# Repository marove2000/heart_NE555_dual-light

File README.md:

# Heart SMD NE555
24 LEDs forming a LED-Heart driven by a NE555 bistable vibrator. A LED-Light runs around the heart. The speed of the running LED-light can be modified by the potentiomenter
This soldering Kit requires first experience in SMD-Soldering and is a very good practice for the size 0805.

- Status: **Complete**
- Difficulty: **3/5**

### Parts List

| Description                   |  Name  | Quantity |
|-------------------------------|:------:|:--------:|
| SMD LED 0805 red              | D5-D28 |    24    |
| SMD Capacitor 10nF            |   C1   |     1    |
| SMD Capacitor 100n            |  C2,C3 |     2    |
| SMD Capacitor 1uF		|   C4	 |     1    |
| SMD Diode 1N4007              |  D1-D2 |     2    |
| SMD Push Button               |   SW1  |     1    |
| SMD Sliding Switch            |   SW2  |     1    |
| RV1 Potentiometer             |   RV1  |     1    |
| SMD Resistor 0805 1k          |   R2   |     1    |
| SMD Resistor 0805 100k        |   R3   |     1    |
| SMD Resistor 0805 47R         |   R5   |     1    |
| NE555 SOIC-8                  |   U1   |     1    |
| CD4017 SOP-16                 |  U2,U3 |     2    |
| CR2032 Battery Holder (SMD)   |   BT1  |     1    |
| CR2032 Battery (not included) |        |     1    |

### Manual
You can find the manual and pictures of every step here: https://github.com/Binary-Kitchen/SolderingTutorial

### Buy Kits

You can also buy a ready to make soldering-kit @ [shop.blinkyparts.com](https://shop.blinkyparts.com/de/SMD-LED-Herz-mit-NE555-SMD-Bausatz-mit-Herz/blink232542).

### Copyright and Authorship

- Board: [CC-BY-SA 4.0](https://creativecommons.org/licenses/by-sa/4.0/) - [Timo Schindler @ blinkyparts.com](https://shop.blinkyparts.com)
- CR2032 battery holder footprint: [CC-BY 4.0](https://creativecommons.org/licenses/by/4.0/) - Sparkfun (https://github.com/sparkfun/SparkFun-KiCad-Libraries)

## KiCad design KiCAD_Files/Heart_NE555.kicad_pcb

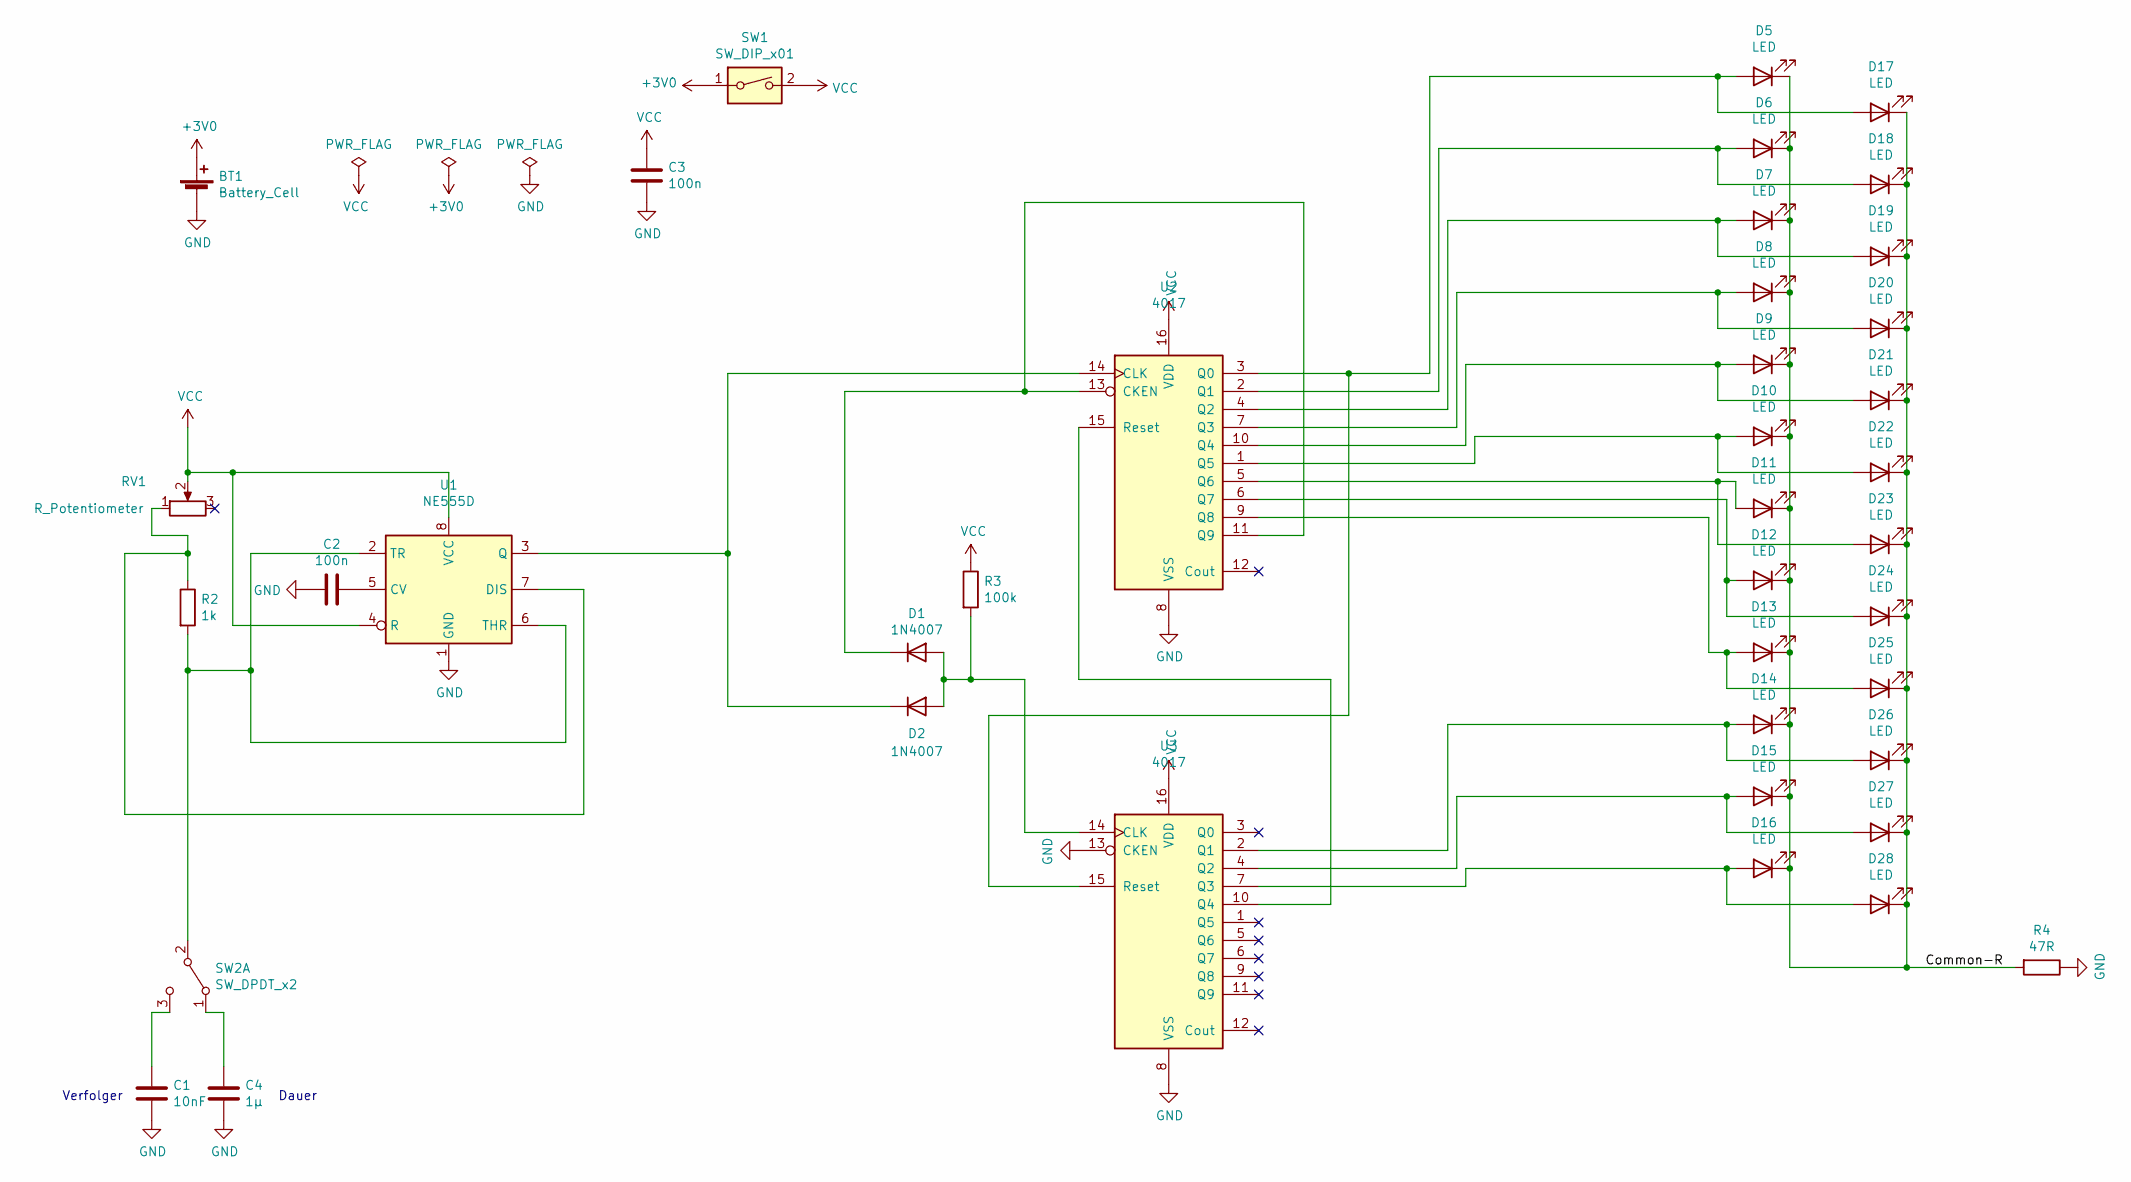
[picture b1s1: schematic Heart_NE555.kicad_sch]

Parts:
BT1: Battery_Cell; BatteryHolder_Keystone_1060_1x2032_HandSoldering
C1: 10nF; C_0805_2012Metric_Pad1.18x1.45mm_HandSolder
C2, C3: 100n; C_0805_2012Metric_Pad1.18x1.45mm_HandSolder
C4: 1µ; C_0805_2012Metric_Pad1.18x1.45mm_HandSolder
D1, D2: 1N4007; D_SOD-123_handsolder
D5, D6, D7, D8, D9, D10, D11, D12, D13, D14, D15, D16, D17, D18, D19, D20, D21, D22, D23, D24, D25, D26, D27, D28: LED; LED_0805_2012Metric_Pad1.15x1.40mm_HandSolder
R2: 1k; R_0805_2012Metric_Pad1.20x1.40mm_HandSolder
R3: 100k; R_0805_2012Metric_Pad1.20x1.40mm_HandSolder
R4: 47R; R_0805_2012Metric_Pad1.20x1.40mm_HandSolder
RV1: R_Potentiometer; Potentiometer_Vishay_TS53YJ_Vertical
SW1: SW_DIP_x01; Push_Button
SW2: SW_DPDT_x2; smd_switch_slide
U1: NE555D; SOIC-8_3.9x4.9mm_P1.27mm
U2, U3: 4017; SOP-16_4.4x10.4mm_P1.27mm

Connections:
+3V0: BT1.1 (+), SW1.1
/Common-R: D5.1 (K), D6.1 (K), D7.1 (K), D8.1 (K), D9.1 (K), D10.1 (K), D11.1 (K), D12.1 (K), D13.1 (K), D14.1 (K), D15.1 (K), D16.1 (K), D17.1 (K), D18.1 (K), D19.1 (K), D20.1 (K), D21.1 (K), D22.1 (K), D23.1 (K), D24.1 (K), D25.1 (K), D26.1 (K), D27.1 (K), D28.1 (K), R4.2
GND: BT1.2 (-), C1.2, C2.2, C3.2, C4.2, R4.1, U1.1 (GND), U2.8 (VSS), U3.8 (VSS), U3.13 (CKEN)
unnamed: C1.1, SW2.3 (C)
unnamed: C2.1, U1.5 (CV)
unnamed: C4.1, SW2.1 (A)
unnamed: D1.1 (K), U2.11 (Q9), U2.13 (CKEN)
unnamed: D1.2 (A), D2.2 (A), R3.2, U3.14 (CLK)
unnamed: D2.1 (K), U1.3 (Q), U2.14 (CLK)
unnamed: D10.2 (A), D22.2 (A), U2.1 (Q5)
unnamed: D11.2 (A), D23.2 (A), U2.5 (Q6)
unnamed: D12.2 (A), D24.2 (A), U2.6 (Q7)
unnamed: D13.2 (A), D25.2 (A), U2.9 (Q8)
unnamed: D14.2 (A), D26.2 (A), U3.2 (Q1)
unnamed: D15.2 (A), D27.2 (A), U3.4 (Q2)
unnamed: D16.2 (A), D28.2 (A), U3.7 (Q3)
unnamed: D5.2 (A), D17.2 (A), U2.3 (Q0), U3.15 (Reset)
unnamed: D6.2 (A), D18.2 (A), U2.2 (Q1)
unnamed: D7.2 (A), D19.2 (A), U2.4 (Q2)
unnamed: D8.2 (A), D20.2 (A), U2.7 (Q3)
unnamed: D9.2 (A), D21.2 (A), U2.10 (Q4)
unnamed: R2.1, RV1.1, U1.7 (DIS)
unnamed: R2.2, SW2.2 (B), U1.2 (TR), U1.6 (THR)
unnamed: U2.15 (Reset), U3.10 (Q4)
VCC: C3.1, R3.1, RV1.2, SW1.2, U1.4 (R), U1.8 (VCC), U2.16 (VDD), U3.16 (VDD)

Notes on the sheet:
Verfolger
Dauer

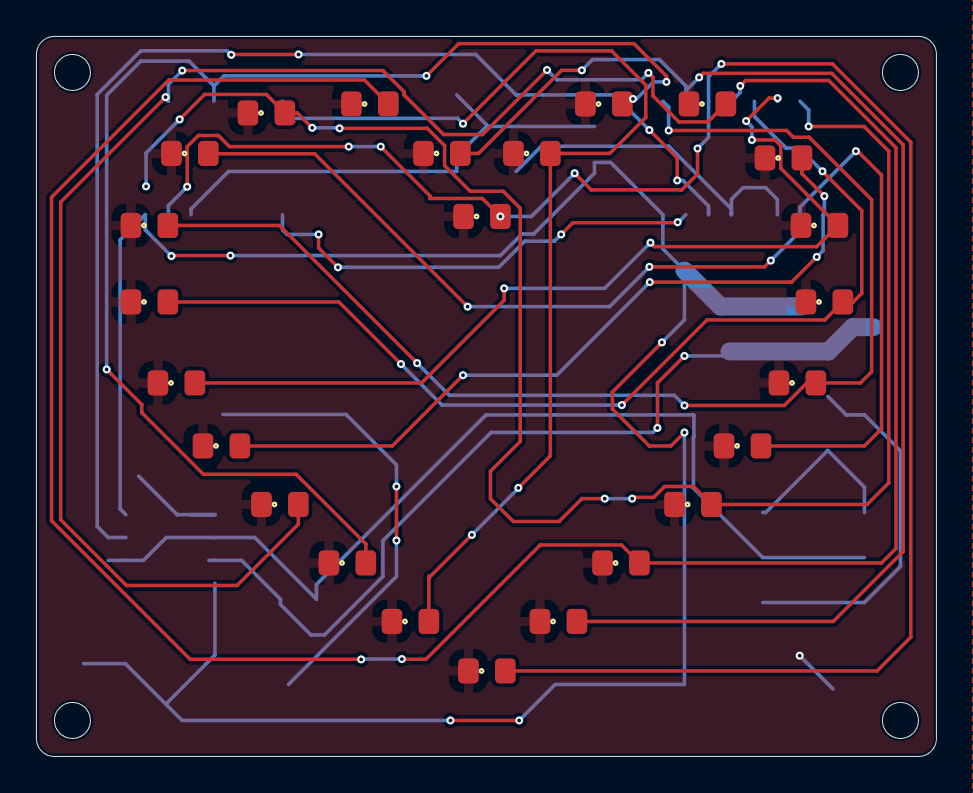
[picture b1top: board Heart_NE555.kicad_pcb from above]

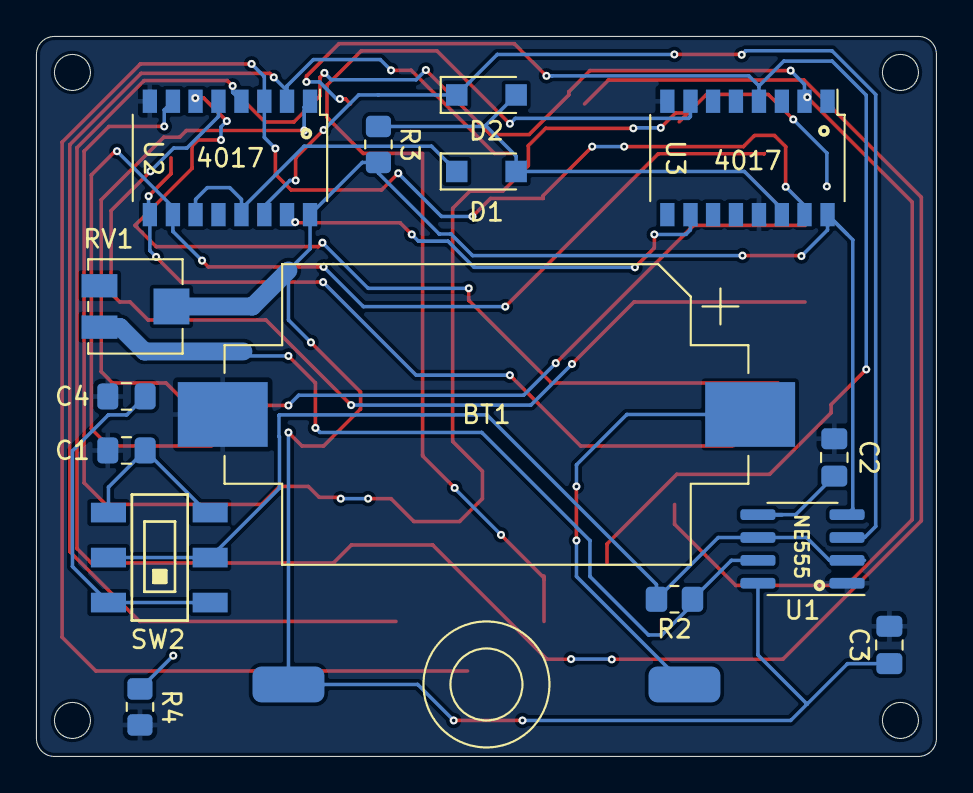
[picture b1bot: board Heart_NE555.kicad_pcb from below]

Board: 2 copper layers, 50.0 x 40.0 mm, 40 parts (16 on the bottom side), 25 nets.

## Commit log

2024-01-22 inital commit
